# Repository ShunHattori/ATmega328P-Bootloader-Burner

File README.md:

# UNO_Bootloader_Burner
 Arduino UNO ブートローダ書き込みシールド

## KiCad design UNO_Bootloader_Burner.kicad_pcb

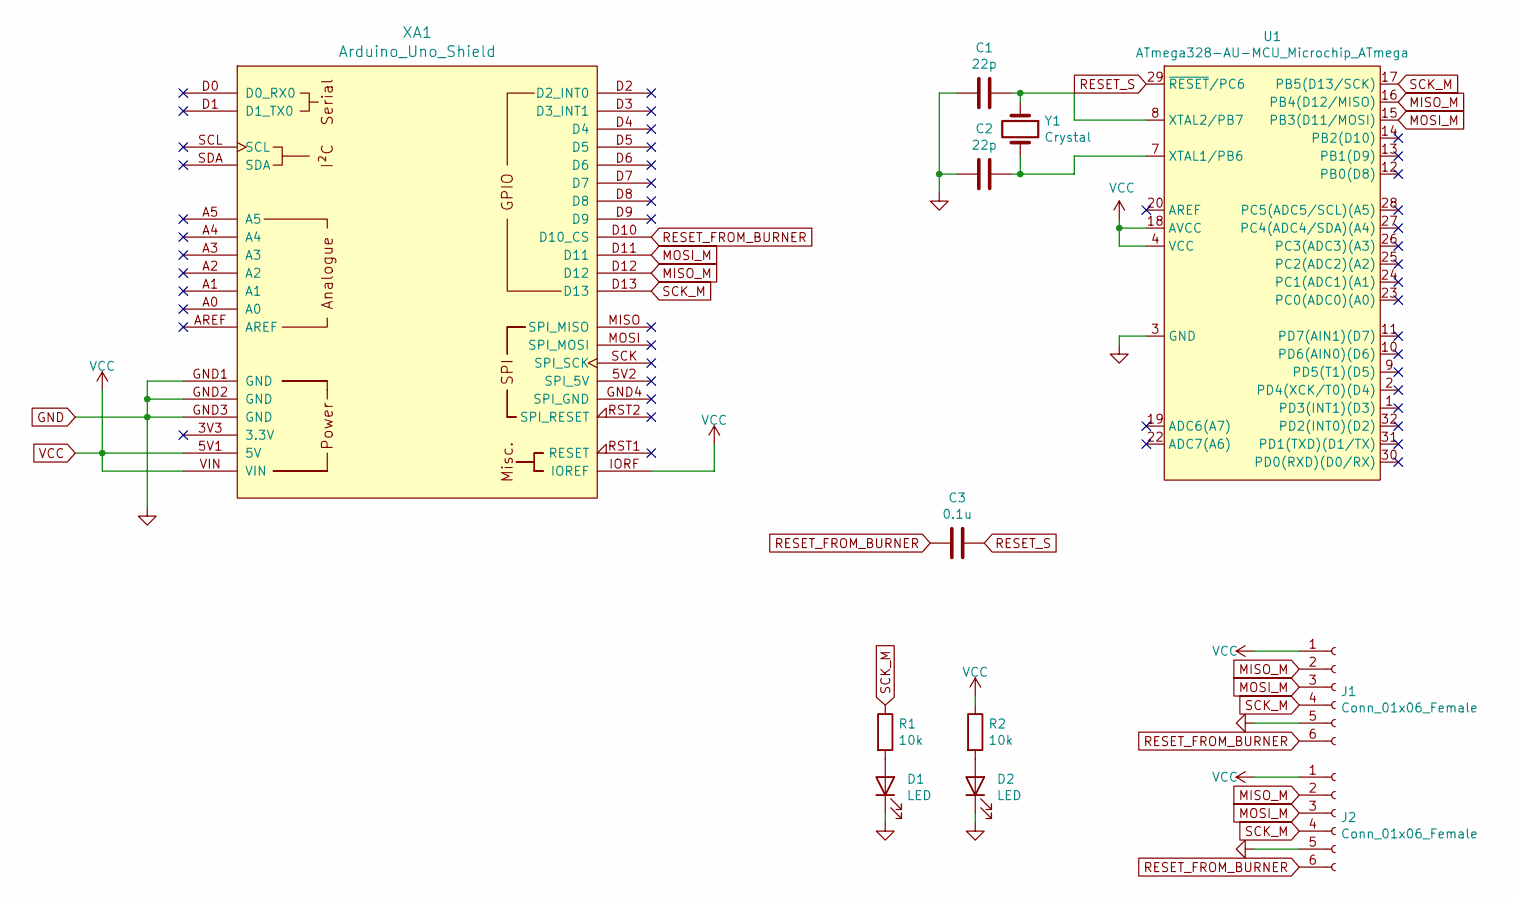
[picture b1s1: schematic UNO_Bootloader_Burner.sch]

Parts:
C1, C2: 22p; C_0603_1608Metric
C3: 0.1u; C_0603_1608Metric
D1, D2: LED; LED_0603_1608Metric
J1: Conn_01x06_Female; PinSocket_1x06_P2.54mm_Vertical
J2: Conn_01x06_Female; PinSocket_2x03_P2.54mm_Vertical
R1, R2: 10k; R_0603_1608Metric
U1: ATmega328-AU-MCU_Microchip_ATmega; TQFP-32_7x7mm_P0.8mm
XA1: Arduino_Uno_Shield
Y1: Crystal; Crystal_HC18-U_Vertical

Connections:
GND: C1.2, C2.2, D1.1 (K), D2.1 (K), J1.5, J2.5, U1.3 (GND), U1.5 (GND), U1.21 (GND), XA1.GND1 (GND), XA1.GND2 (GND), XA1.GND3 (GND)
MISO_M: J1.2, J2.2, U1.16 (PB4(D12/MISO)), XA1.D12
MOSI_M: J1.3, J2.3, U1.15 (PB3(D11/MOSI)), XA1.D11
unnamed: C1.1, U1.8 (XTAL2/PB7), Y1.1
unnamed: C2.1, U1.7 (XTAL1/PB6), Y1.2
unnamed: D1.2 (A), R1.2
unnamed: D2.2 (A), R2.2
RESET_FROM_BURNER: C3.2, J1.6, J2.6, XA1.D10 (D10_CS)
RESET_S: C3.1, U1.29 (~RESET~/PC6)
SCK_M: J1.4, J2.4, R1.1, U1.17 (PB5(D13/SCK)), XA1.D13
VCC: J1.1, J2.1, R2.1, U1.4 (VCC), U1.6 (VCC), U1.18 (AVCC), XA1.5V1 (5V), XA1.IORF (IOREF), XA1.VIN

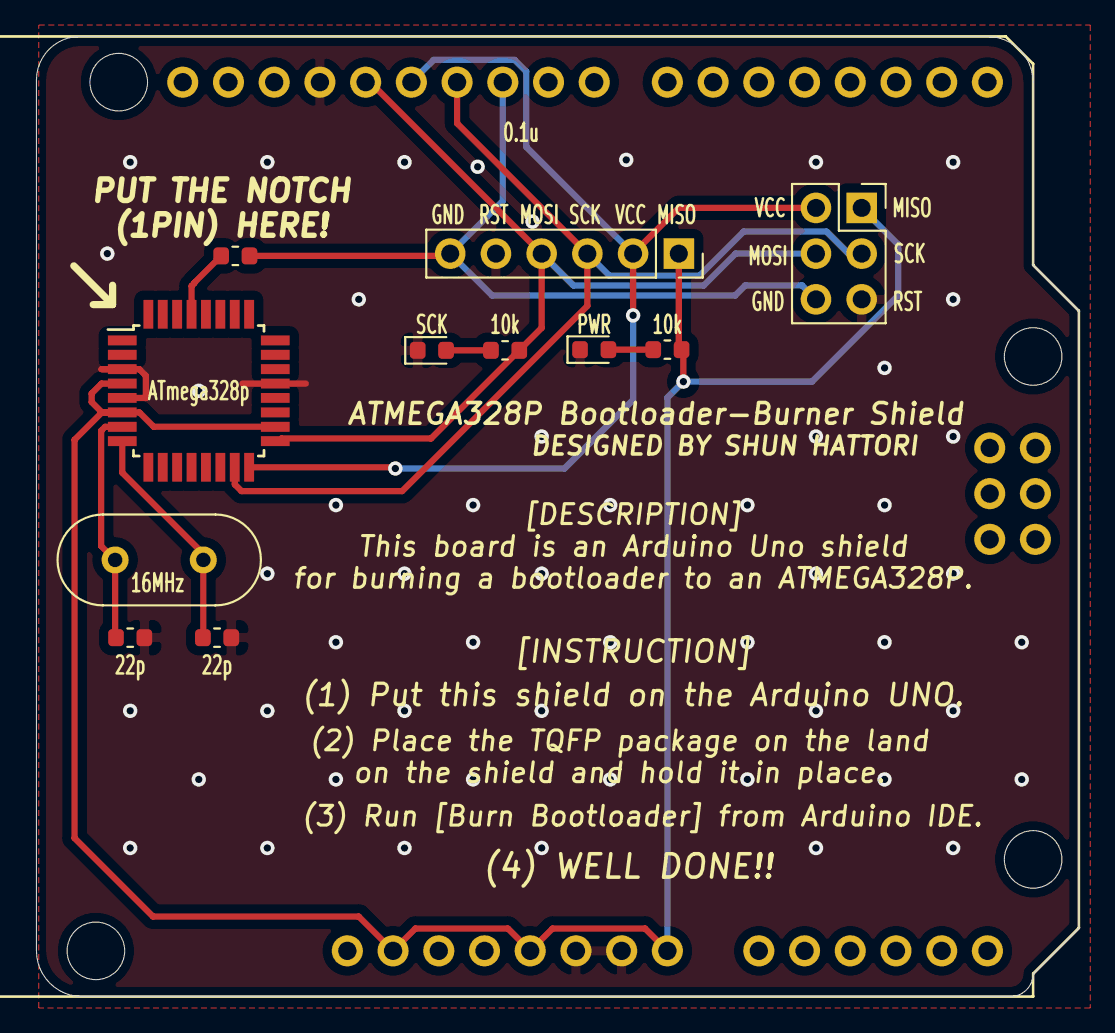
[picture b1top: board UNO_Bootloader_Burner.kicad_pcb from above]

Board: 2 copper layers, 57.9 x 53.3 mm, 12 parts (0 on the bottom side), 11 nets.

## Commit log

2020-12-30 add QR CODE to the PCB file
2020-12-30 update library path
2021-01-24 change osc component, update osc pattern
